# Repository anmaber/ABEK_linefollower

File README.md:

# ABEK_linefollower

Project created during Mobile Robots classes.

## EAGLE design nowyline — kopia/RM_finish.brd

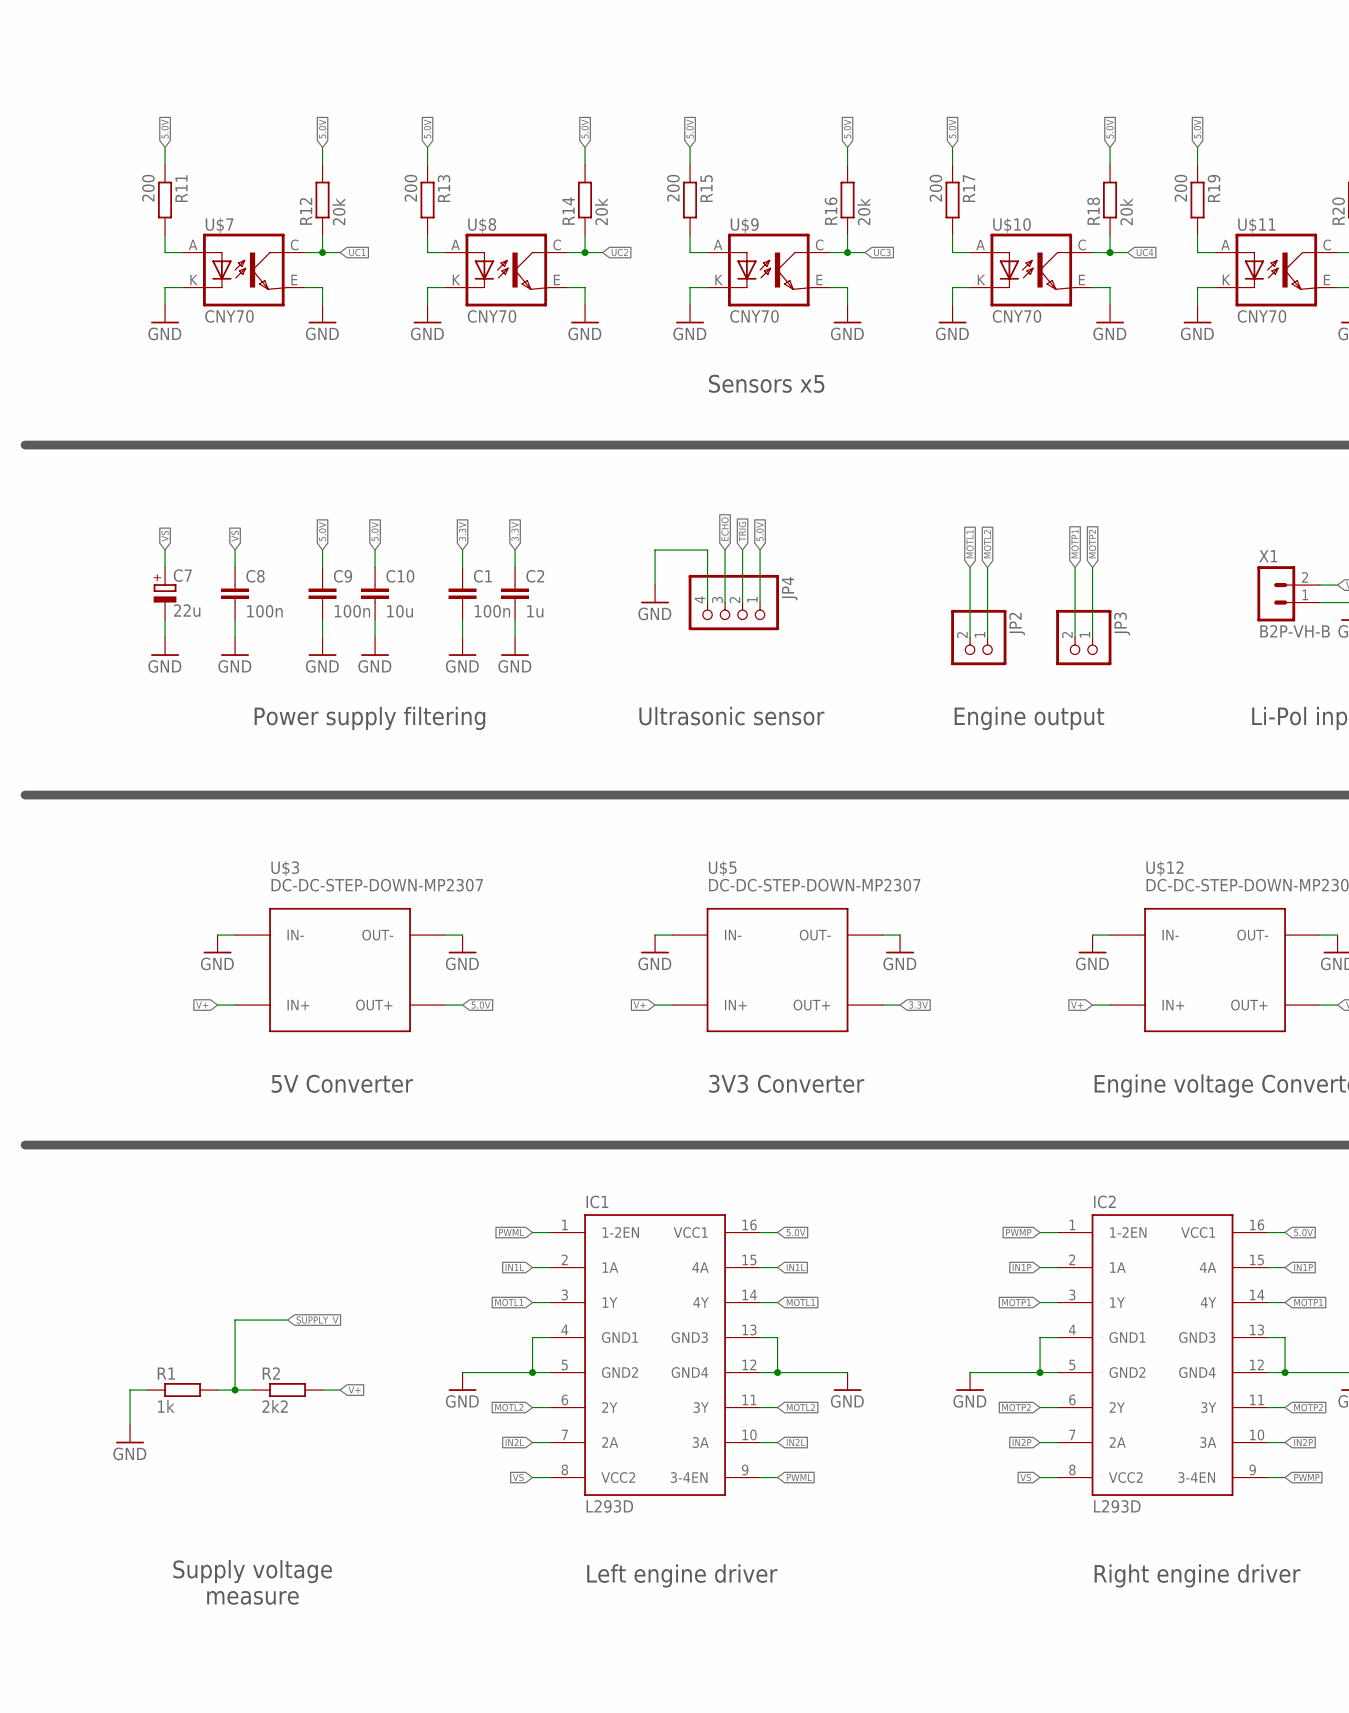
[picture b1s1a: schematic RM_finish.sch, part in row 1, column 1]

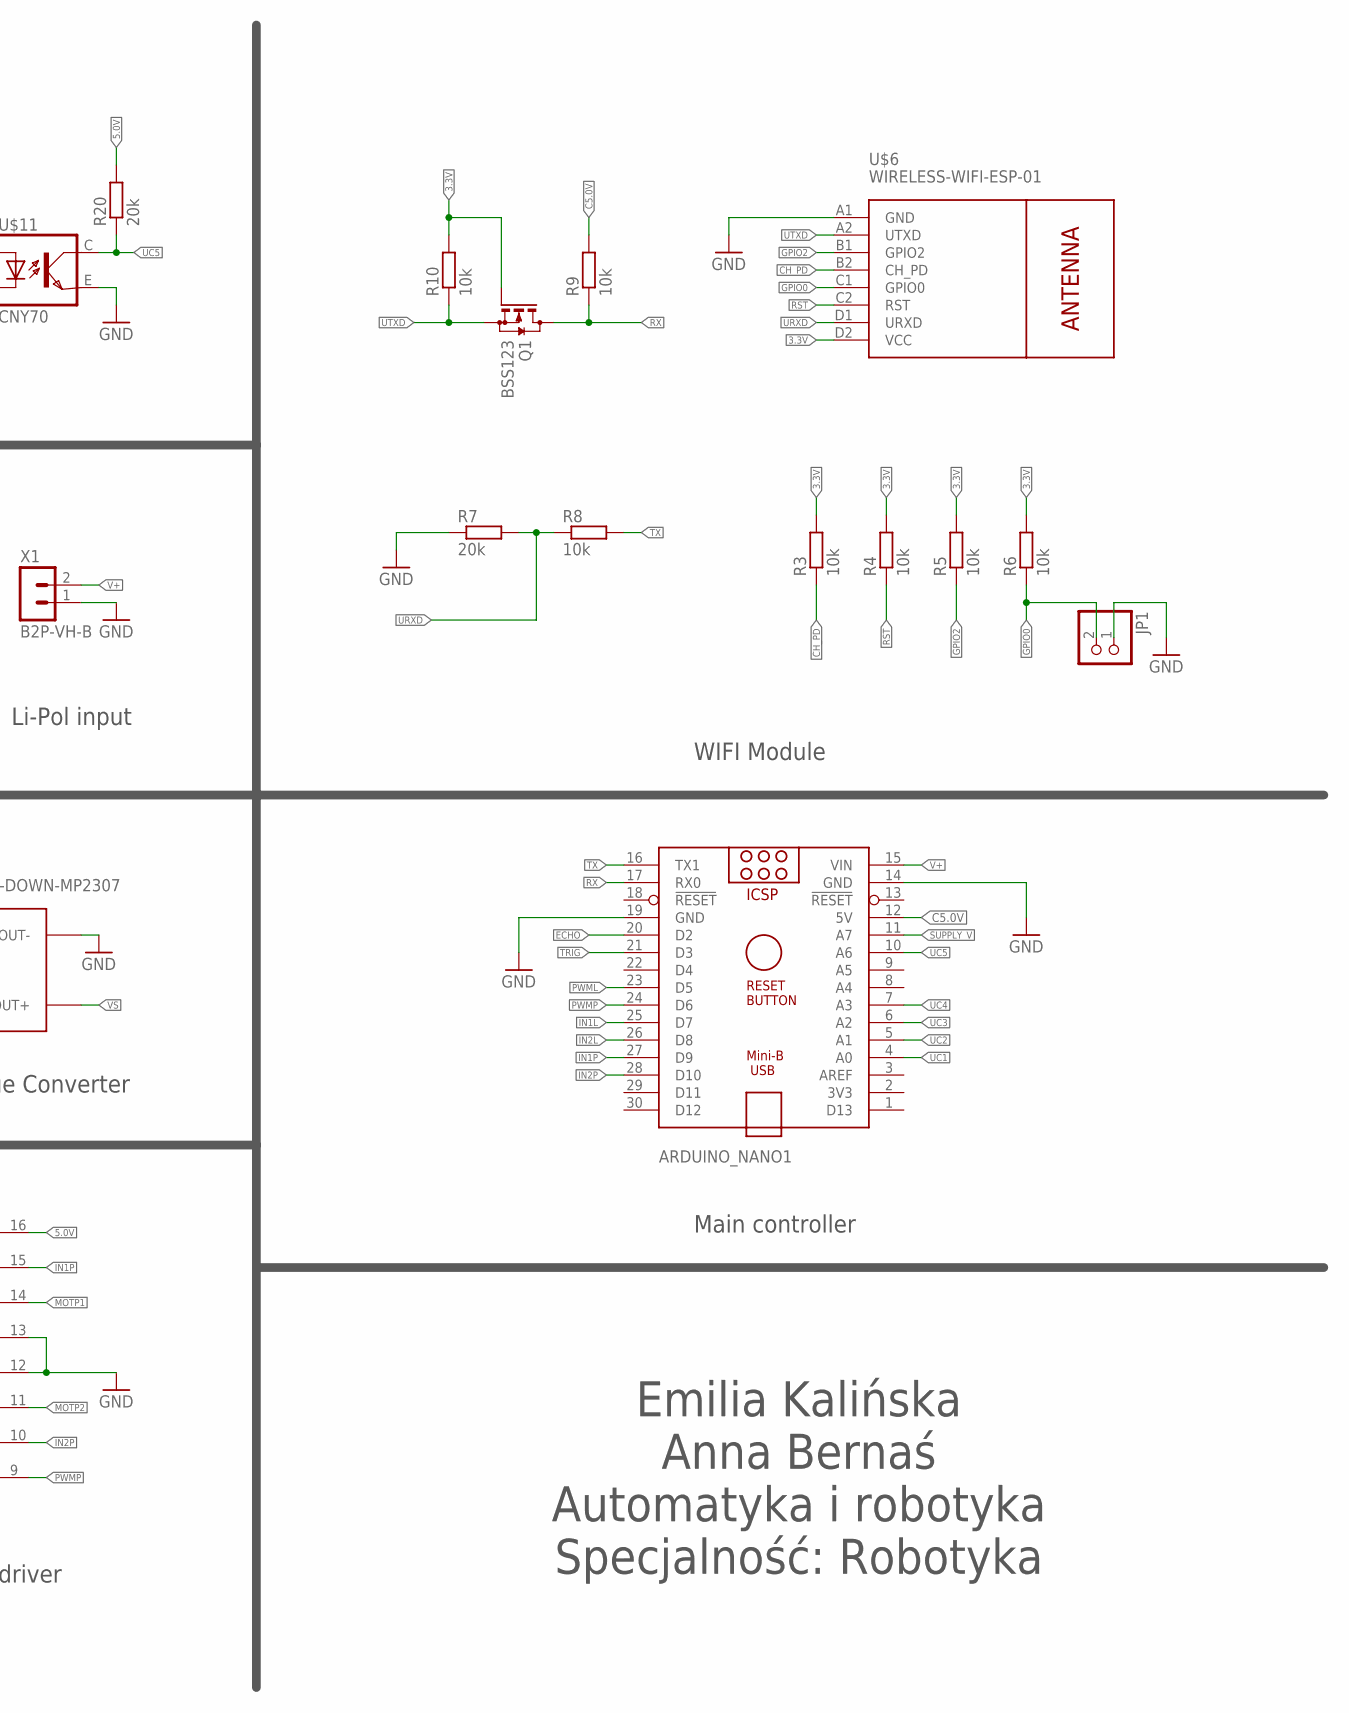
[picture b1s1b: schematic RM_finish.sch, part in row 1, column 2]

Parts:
ARDUINO_NANO1: ARDUINO_NANO
C1, C8, C9: 100n; C0805
C2: 1u; C0805
C7: 22u; 153CLV-0405
C10: 10u; C0805
IC1, IC2: L293D; DIL16
JP1, JP2, JP3: PINHD-1X2; 1X02
JP4: PINHD-1X4; 1X04
Q1: BSS123; SOT23
R1: 1k; R0805
R2: 2k2; R0805
R3, R4, R5, R6, R8, R9, R10: 10k; R0805
R7, R12, R14, R16, R18, R20: 20k; R0805
R11, R13, R15, R17, R19: 200; R0805
U$3, U$5, U$12: DC-DC-STEP-DOWN-MP2307
U$6: WIRELESS-WIFI-ESP-01
U$7, U$8, U$9, U$10, U$11: CNY70; 4
X1: B2P-VH-B; B2P-VH

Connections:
3.3V: C1.1, C2.1, Q1.1 (G), R3.2, R4.2, R5.2, R6.2, R10.2, U$5.OUT+, U$6.D2 (VCC)
5.0V: C9.1, C10.1, IC1.16 (VCC1), IC2.16 (VCC1), JP4.1, R11.1, R12.2, R13.1, R14.2, R15.1, R16.2, R17.1, R18.2, R19.1, R20.2, U$3.OUT+
C5.0V: ARDUINO_NANO1.12 (5V), R9.2
CH_PD: R3.1, U$6.B2 (CH_PD)
ECHO: ARDUINO_NANO1.20 (D2), JP4.3
GND: ARDUINO_NANO1.14 (GND), ARDUINO_NANO1.19 (GND), C1.2, C2.2, C7.-, C8.2, C9.2, C10.2, IC1.4 (GND1), IC1.5 (GND2), IC1.12 (GND4), IC1.13 (GND3), IC2.4 (GND1), IC2.5 (GND2), IC2.12 (GND4), IC2.13 (GND3), JP1.1, JP4.4, R1.1, R7.1, U$3.IN-, U$3.OUT-, U$5.IN-, U$5.OUT-, U$6.A1 (GND), U$7.E (EMI), U$7.K (C), U$8.E (EMI), U$8.K (C), U$9.E (EMI), U$9.K (C), U$10.E (EMI), U$10.K (C), U$11.E (EMI), U$11.K (C), U$12.IN-, U$12.OUT-, X1.1
GPIO0: JP1.2, R6.1, U$6.C1 (GPIO0)
GPIO2: R5.1, U$6.B1 (GPIO2)
IN1L: ARDUINO_NANO1.25 (D7), IC1.2 (1A), IC1.15 (4A)
IN1P: ARDUINO_NANO1.27 (D9), IC2.2 (1A), IC2.15 (4A)
IN2L: ARDUINO_NANO1.26 (D8), IC1.7 (2A), IC1.10 (3A)
IN2P: ARDUINO_NANO1.28 (D10), IC2.7 (2A), IC2.10 (3A)
MOTL1: IC1.3 (1Y), IC1.14 (4Y), JP2.2
MOTL2: IC1.6 (2Y), IC1.11 (3Y), JP2.1
MOTP1: IC2.3 (1Y), IC2.14 (4Y), JP3.2
MOTP2: IC2.6 (2Y), IC2.11 (3Y), JP3.1
unnamed: R11.2, U$7.A
unnamed: R13.2, U$8.A
unnamed: R15.2, U$9.A
unnamed: R17.2, U$10.A
unnamed: R19.2, U$11.A
PWML: ARDUINO_NANO1.23 (D5), IC1.1 (1-2EN), IC1.9 (3-4EN)
PWMP: ARDUINO_NANO1.24 (D6), IC2.1 (1-2EN), IC2.9 (3-4EN)
RST: R4.1, U$6.C2 (RST)
RX: ARDUINO_NANO1.17 (RX0), Q1.3 (D), R9.1
SUPPLY_V: ARDUINO_NANO1.11 (A7), R1.2, R2.1
TRIG: ARDUINO_NANO1.21 (D3), JP4.2
TX: ARDUINO_NANO1.16 (TX1), R8.2
UC1: ARDUINO_NANO1.4 (A0), R12.1, U$7.C (COL)
UC2: ARDUINO_NANO1.5 (A1), R14.1, U$8.C (COL)
UC3: ARDUINO_NANO1.6 (A2), R16.1, U$9.C (COL)
UC4: ARDUINO_NANO1.7 (A3), R18.1, U$10.C (COL)
UC5: ARDUINO_NANO1.10 (A6), R20.1, U$11.C (COL)
URXD: R7.2, R8.1, U$6.D1 (URXD)
UTXD: Q1.2 (S), R10.1, U$6.A2 (UTXD)
V+: ARDUINO_NANO1.15 (VIN), R2.2, U$3.IN+, U$5.IN+, U$12.IN+, X1.2
VS: C7.+, C8.1, IC1.8 (VCC2), IC2.8 (VCC2), U$12.OUT+

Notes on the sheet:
WIFI Module
Main controller
Sensors x5
Power supply filtering
Ultrasonic sensor
Engine output
Li-Pol input
5V Converter
3V3 Converter
Engine voltage Converter
Supply voltage measure
Left engine driver
Right engine driver
Emilia Kalińska Anna Bernaś Automatyka i robotyka Specjalność: Robotyka

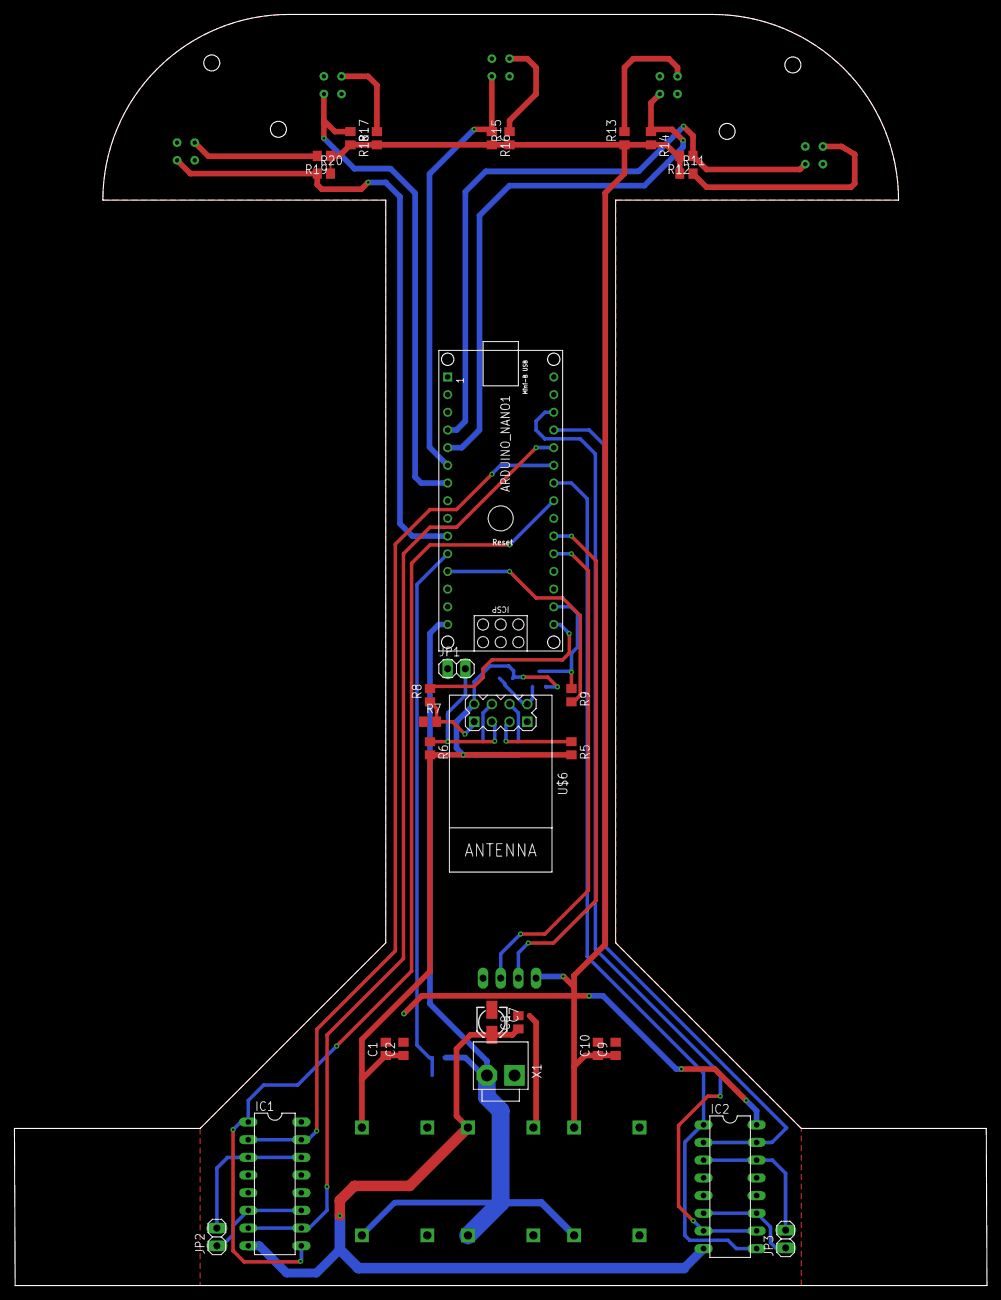
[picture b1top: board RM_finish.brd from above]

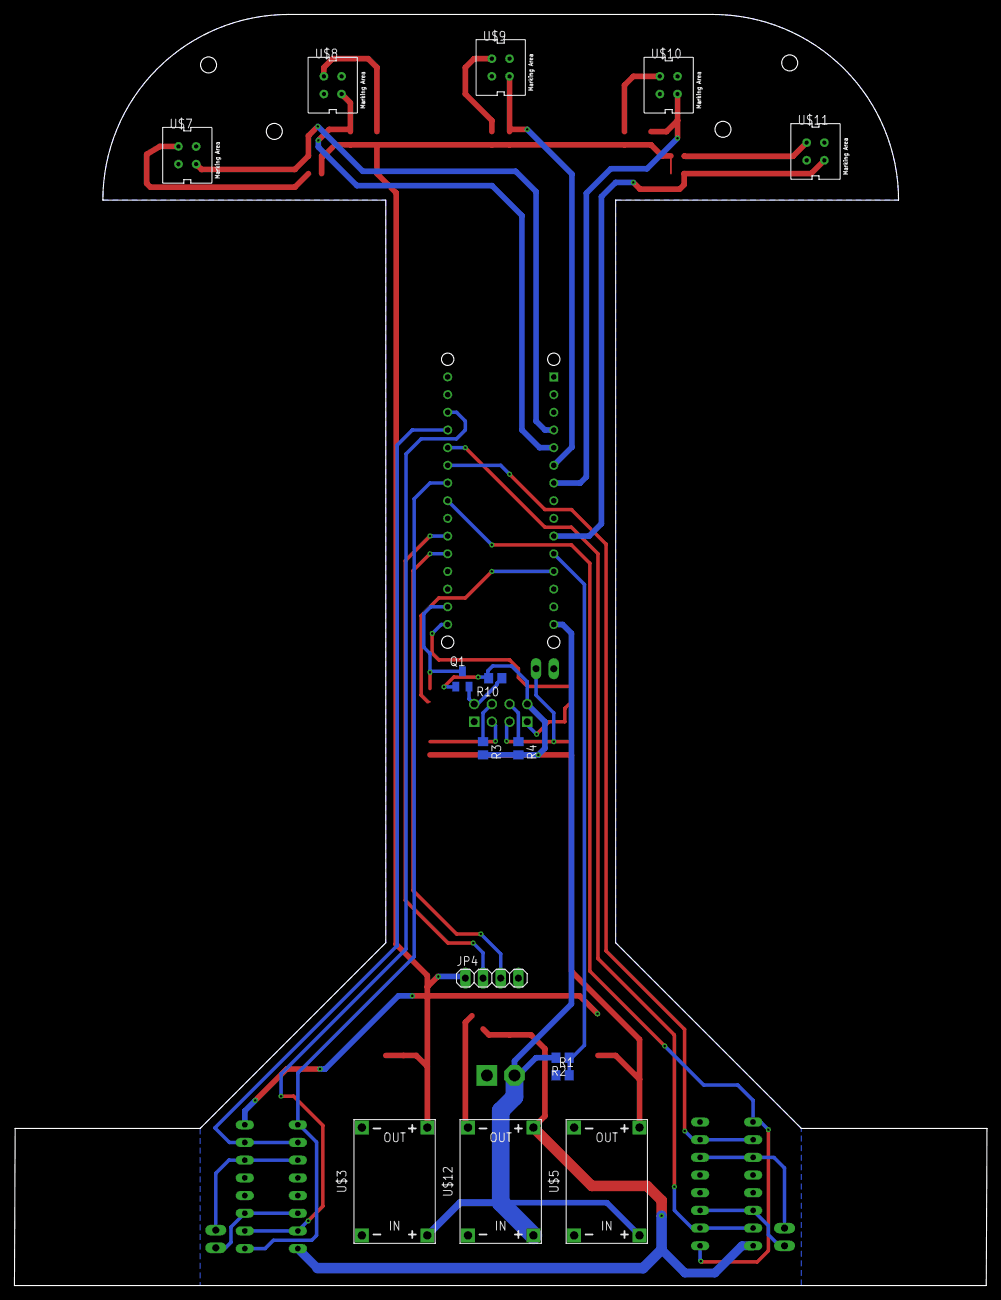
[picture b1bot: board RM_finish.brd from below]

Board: 2 copper layers, 139.7 x 182.6 mm, 44 parts (15 on the bottom side), 37 nets.

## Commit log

2020-05-08 documenntation added
2020-05-08 Schemat płytki PCB
2020-05-08 electronics
2020-05-08 Wytrawienie_dół
2020-05-08 Wytrawienie_góra
2020-05-08 photos
2020-05-08 Płytka PCB
2020-05-08 pictures v2
2020-05-08 updated docummentation
2020-05-21 ABEK Eagle
2020-05-21 First test program
2020-06-07 Trying to use Blynk, ESP and arduino
2020-06-07 Sensor implementation
2020-06-14 works during comparison, first try PID
2020-06-14 pid inne warunki
2020-06-14 Working PID
2020-06-16 wifi and pid works
2020-06-17 cleaned up repo

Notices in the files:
parts and their libraries:
diy-modules: Released under the Creative Commons Attribution 4.0 International License: http://creativecommons.org/licenses/by/4.0
